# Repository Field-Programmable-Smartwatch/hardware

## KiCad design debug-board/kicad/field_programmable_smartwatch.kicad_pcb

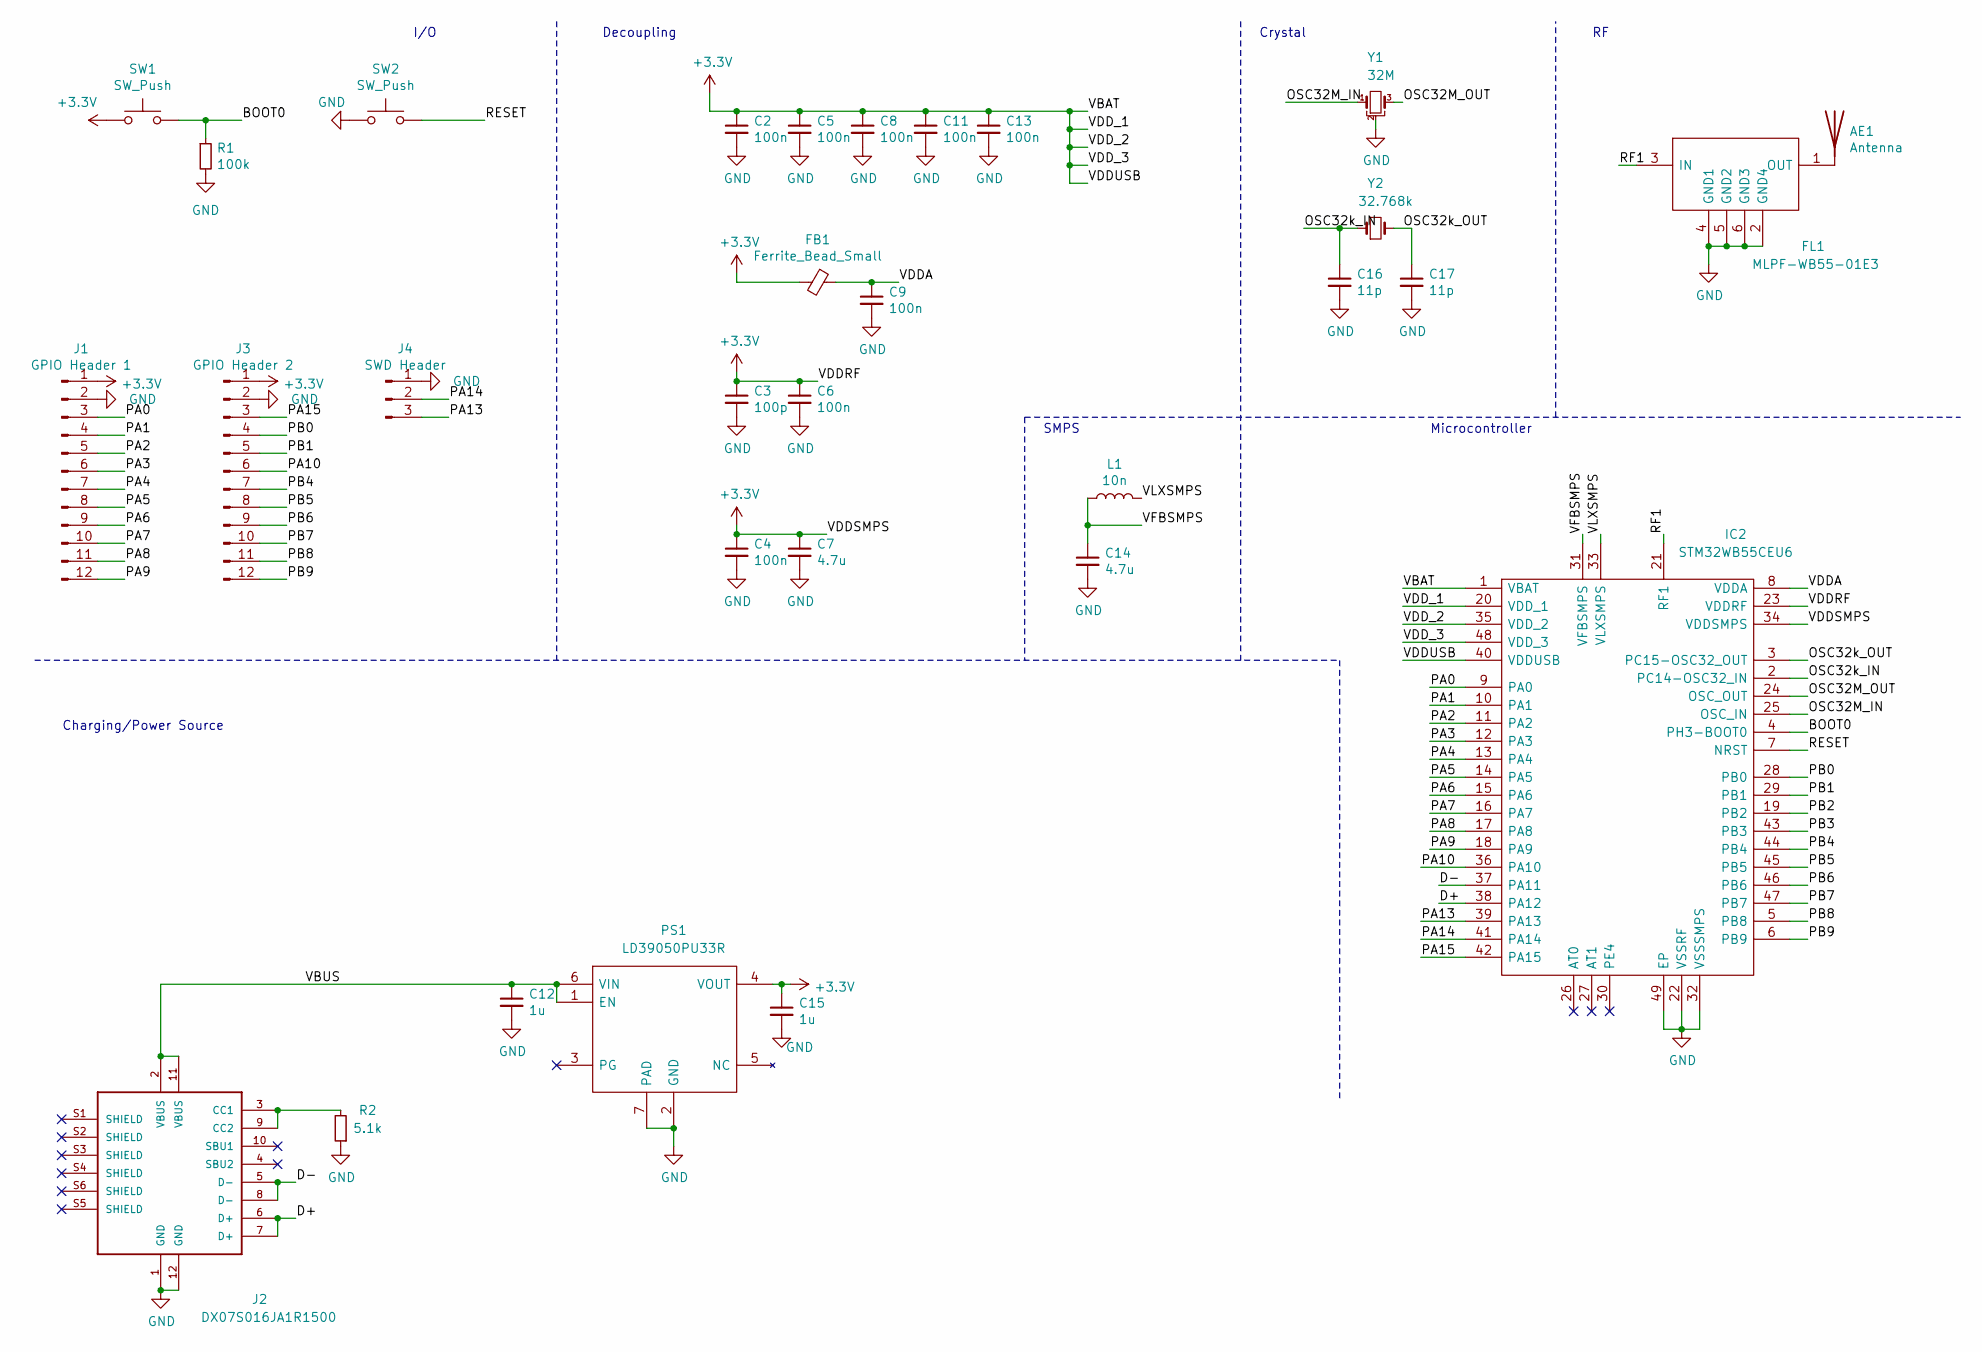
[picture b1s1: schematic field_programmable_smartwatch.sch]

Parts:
AE1: Antenna; W3006; Mfg Part # W3006
C2, C4, C5, C6, C8, C9, C11, C13: 100n; C_0402_1005Metric; Manufacturer_Part_Number CL05B104KO5NNNC; LCSC Part # C1525
C3: 100p; C_0402_1005Metric; Manufacturer_Part_Number 0402CG101J500NT; LCSC Part # C1546
C7, C14: 4.7u; C_0402_1005Metric; Manufacturer_Part_Number CL05A475MP5NRNC; LCSC Part # C23733
C12: 1u; C_0603_1608Metric; Manufacturer_Part_Number CL10A105KB8NNNC; LCSC Part # C15849
C15: 1u; C_0402_1005Metric; Manufacturer_Part_Number CL05A105KA5NQNC; LCSC Part # C52923
C16, C17: 11p; C_0402_1005Metric; Mfg Part # GCQ1555C1H110GB01D
FB1: Ferrite_Bead_Small; L_0603_1608Metric; Manufacturer_Part_Number BLM18PG121SN1D; LCSC Part # C73100
FL1: MLPF-WB55-01E3; MLPFWB5501E3; Manufacturer_Part_Number MLPF-WB55-01E3; Mouser Part Number 511-MLPF-WB55-01E3
IC2: STM32WB55CEU6; QFN50P700X700X65-49N-D; Manufacturer_Part_Number STM32WB55CEU6; Mouser Part Number 511-STM32WB55CEU6
J1: GPIO Header 1; PinHeader_1x12_P2.54mm_Vertical
J2: DX07S016JA1R1500; JAE_DX07S016JA1R1500; Manufacturer_Part_Number DX07S016JA1R1500
J3: GPIO Header 2; PinHeader_1x12_P2.54mm_Vertical
J4: SWD Header; PinHeader_1x03_P2.54mm_Vertical
L1: 10n; L_0402_1005Metric; Manufacturer_Part_Number SDCL1005C10NJTDF; LCSC Part # C27147
PS1: LD39050PU33R; SON95P300X300X100-7N-D; Manufacturer_Part_Number LD39050PU33R; Mouser Part Number 511-LD39050PU33R
R1: 100k; R_0402_1005Metric; Manufacturer_Part_Number 0402WGF1003TCE; LCSC Part # C25741
R2: 5.1k; R_0402_1005Metric; Manufacturer_Part_Number 0402WGF5101TCE; LCSC Part # C25905
SW1, SW2: SW_Push; SW_Push_SPST_NO_Alps_SKRK; Mfg Part # SKRKAHE020
Y1: 32M; OSCCC200X160X50N; Mfg Part # NX2016SA-32MHZ-EXS00A-CS11336
Y2: 32.768k; NX3215SA-32.768K-STD-MUA-14; Mfg Part # NX3215SA-32.768K-STD-MUA-14

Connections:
+3V3: C2.1, C3.1, C4.1, C5.1, C6.1, C7.1, C8.1, C11.1, C13.1, C15.1, FB1.2, IC2.1 (VBAT), IC2.20 (VDD_1), IC2.23 (VDDRF), IC2.34 (VDDSMPS), IC2.35 (VDD_2), IC2.40 (VDDUSB), IC2.48 (VDD_3), J1.1, J3.1, PS1.4 (VOUT), SW1.1
/BOOT0: IC2.4 (PH3-BOOT0), R1.1, SW1.2
/D+: IC2.38 (PA12), J2.6 (D+), J2.7 (D+)
/D-: IC2.37 (PA11), J2.5 (D-), J2.8 (D-)
/OSC32M_IN: IC2.25 (OSC_IN), Y1.1
/OSC32M_OUT: IC2.24 (OSC_OUT), Y1.3
/OSC32k_IN: C16.1, IC2.2 (PC14-OSC32_IN), Y2.1
/OSC32k_OUT: C17.1, IC2.3 (PC15-OSC32_OUT), Y2.2
/PA0: IC2.9 (PA0), J1.3
/PA1: IC2.10 (PA1), J1.4
/PA2: IC2.11 (PA2), J1.5
/PA3: IC2.12 (PA3), J1.6
/PA4: IC2.13 (PA4), J1.7
/PA5: IC2.14 (PA5), J1.8
/PA6: IC2.15 (PA6), J1.9
/PA7: IC2.16 (PA7), J1.10
/PA8: IC2.17 (PA8), J1.11
/PA9: IC2.18 (PA9), J1.12
/PA10: IC2.36 (PA10), J3.6
/PA13: IC2.39 (PA13), J4.3
/PA14: IC2.41 (PA14), J4.2
/PA15: IC2.42 (PA15), J3.3
/PB0: IC2.28 (PB0), J3.4
/PB1: IC2.29 (PB1), J3.5
/PB2: IC2.19 (PB2)
/PB3: IC2.43 (PB3)
/PB4: IC2.44 (PB4), J3.7
/PB5: IC2.45 (PB5), J3.8
/PB6: IC2.46 (PB6), J3.9
/PB7: IC2.47 (PB7), J3.10
/PB8: IC2.5 (PB8), J3.11
/PB9: IC2.6 (PB9), J3.12
/RESET: IC2.7 (NRST), SW2.2
/RF1: FL1.3 (IN), IC2.21 (RF1)
/VBUS: C12.1, J2.2 (VBUS), J2.11 (VBUS), PS1.1 (EN), PS1.6 (VIN)
/VDDA: C9.1, FB1.1, IC2.8 (VDDA)
/VFBSMPS: C14.1, IC2.31 (VFBSMPS), L1.1
/VLXSMPS: IC2.33 (VLXSMPS), L1.2
GND: C2.2, C3.2, C4.2, C5.2, C6.2, C7.2, C8.2, C9.2, C11.2, C12.2, C13.2, C14.2, C15.2, C16.2, C17.2, FL1.2 (GND4), FL1.4 (GND1), FL1.5 (GND2), FL1.6 (GND3), IC2.22 (VSSRF), IC2.32 (VSSSMPS), IC2.49 (EP), J1.2, J2.1 (GND), J2.12 (GND), J3.2, J4.1, PS1.2 (GND), PS1.7 (PAD), R1.2, R2.1, SW2.1, Y1.2
unnamed: AE1.1, FL1.1 (OUT)
unnamed: J2.3 (CC1), J2.9 (CC2), R2.2

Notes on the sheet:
Charging/Power Source
Decoupling
SMPS
Crystal
Microcontroller
I/O

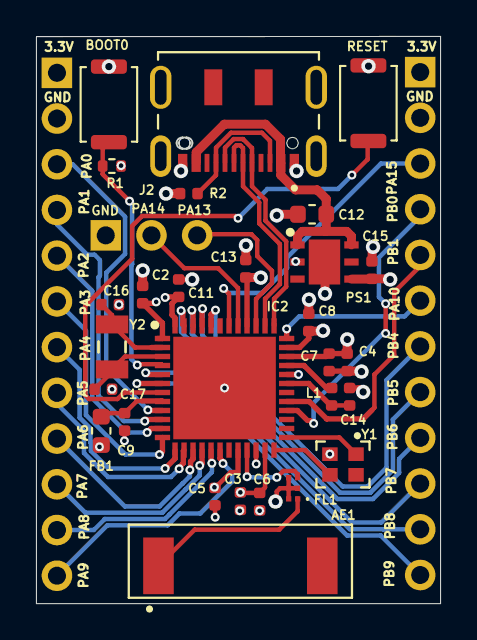
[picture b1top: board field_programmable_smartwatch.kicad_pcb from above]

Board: 4 copper layers, 22.4 x 31.5 mm, 31 parts (0 on the bottom side), 39 nets.

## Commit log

2021-03-05 Reworking debug board design
2021-03-10 Rework debug board design
2021-04-07 Add labels to PCB components. Remove unneeded files
2021-04-07 Remove unneeded files
2021-04-07 Add generated gerber and drill files to gitignore
2021-04-07 Add Makefile and plot script to generate gerber and drill files
2021-04-29 Set via on reset button to GND instead of 3.3V
2021-08-18 Updated debug board
2021-08-26 Move the edge cuts in
2021-08-30 Simplify the PA13 pin trace
2021-08-31 Bring back the boot0 pin button
